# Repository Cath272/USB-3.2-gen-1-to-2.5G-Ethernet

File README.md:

# USB 3.2 gen 1 to 2.5Gb Ethernet
 2.5GbE to USB C using VL162 and RTL8156

 ## VL162

  - 4:2 10Gbps USB Type-C Data Switch

  - Low power consumption with 6mW active at device mode

 ## RTL8156BG 

  - Integrated 10/100/1000M/2.5G transceiver

  - Supports USB 3.0, 2.0, and 1.1

 ## TPS62420

 - 5V to 3.3V DC-DC (600mA)
 - 5V to 0.95V DC-DC (1A)

 ## W25Q16BVSSIG

 - 16Mbit SPI Flash  

 ## LX82405SP
 -2.5GbE Magnetics 
## PCB 
This board uses a 4 layer stackup with a  1.6mm thickness:

- POWER/SIGNAL

- GND
  
- GND
  
- POWER/SIGNAL

High Speed diferential lines need a refrence ground plane so internal planes are ground referance planes for the High speed USB lines

### Schematic:

## PCB Screenshots

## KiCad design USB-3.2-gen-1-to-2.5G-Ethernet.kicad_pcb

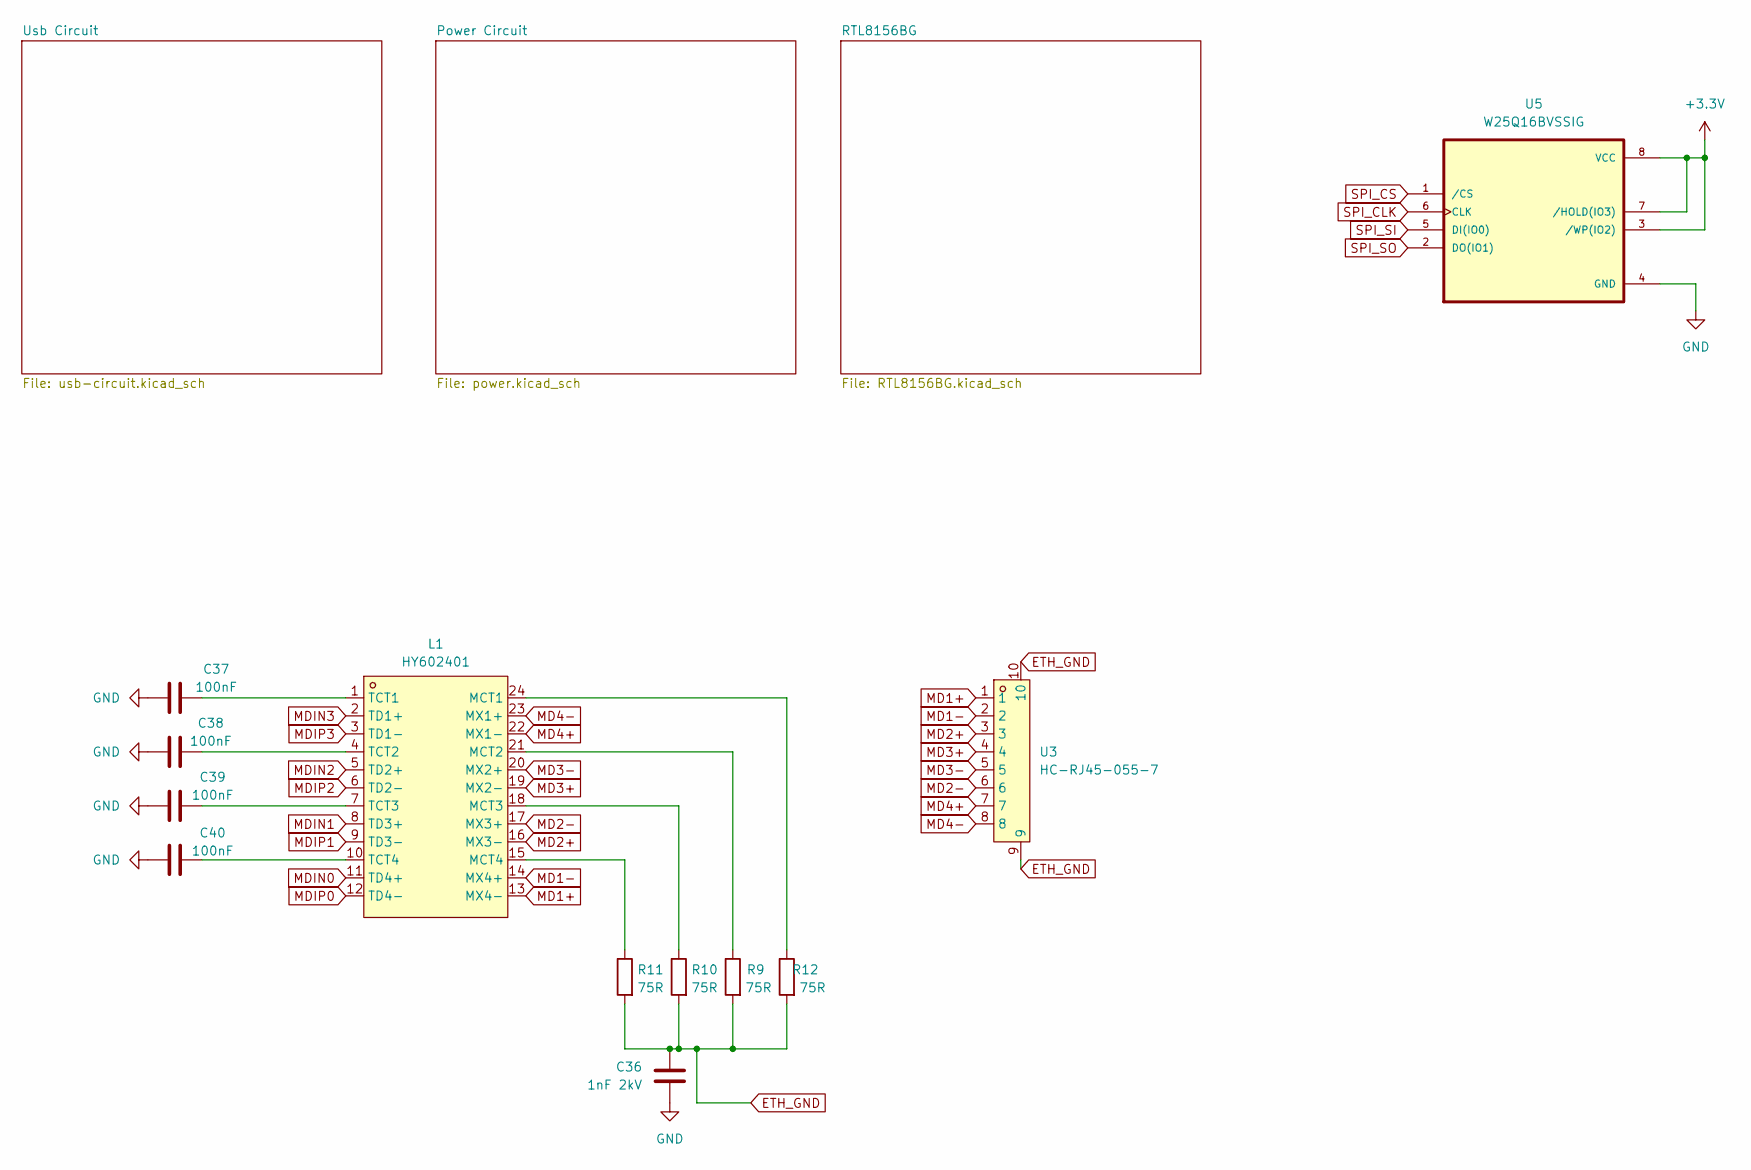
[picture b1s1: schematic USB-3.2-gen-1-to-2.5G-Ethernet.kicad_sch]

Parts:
C36: 1nF 2kV; C_1210_3225Metric
C37, C38, C39, C40: 100nF; C_0402_1005Metric
L1: HY602401; XFMR-SMD_HY602401; LCSC Part C55685
R9, R10, R11, R12: 75R; R_0402_1005Metric
U3: HC-RJ45-055-7; RJ45-SMD_HC-RJ45-055-7_1; LCSC Part C3000213
U5: W25Q16BVSSIG; SOIC-8_L5.3-W5.3-P1.27-LS8.0-BL; PARTREV F

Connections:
+3.3V: U5.3 (/WP(IO2)), U5.7 (/HOLD(IO3)), U5.8 (VCC); also elsewhere on the board
ETH_GND: C36.1, R9.2, R10.2, R11.2, R12.2, U3.9, U3.10
GND: C36.2, C37.2, C38.2, C39.2, C40.2, U5.4 (GND); also elsewhere on the board
LED0: U5.5 (DI(IO0)); also elsewhere on the board
MD1+: L1.13 (MX4-), U3.1
MD1-: L1.14 (MX4+), U3.2
MD2+: L1.16 (MX3-), U3.3
MD2-: L1.17 (MX3+), U3.6
MD3+: L1.19 (MX2-), U3.4
MD3-: L1.20 (MX2+), U3.5
MD4+: L1.22 (MX1-), U3.7
MD4-: L1.23 (MX1+), U3.8
MDIN0: L1.11 (TD4+); also elsewhere on the board
MDIN1: L1.8 (TD3+); also elsewhere on the board
MDIN2: L1.5 (TD2+); also elsewhere on the board
MDIN3: L1.2 (TD1+); also elsewhere on the board
MDIP0: L1.12 (TD4-); also elsewhere on the board
MDIP1: L1.9 (TD3-); also elsewhere on the board
MDIP2: L1.6 (TD2-); also elsewhere on the board
MDIP3: L1.3 (TD1-); also elsewhere on the board
unnamed: L1.24 (MCT1), R12.1
unnamed: L1.21 (MCT2), R9.1
unnamed: L1.18 (MCT3), R10.1
unnamed: L1.15 (MCT4), R11.1
unnamed: C37.1, L1.1 (TCT1)
unnamed: C38.1, L1.4 (TCT2)
unnamed: C39.1, L1.7 (TCT3)
unnamed: C40.1, L1.10 (TCT4)
SPI_CLK: U5.6 (CLK); also elsewhere on the board
SPI_CS: U5.1 (/CS); also elsewhere on the board
SPI_SO: U5.2 (DO(IO1)); also elsewhere on the board

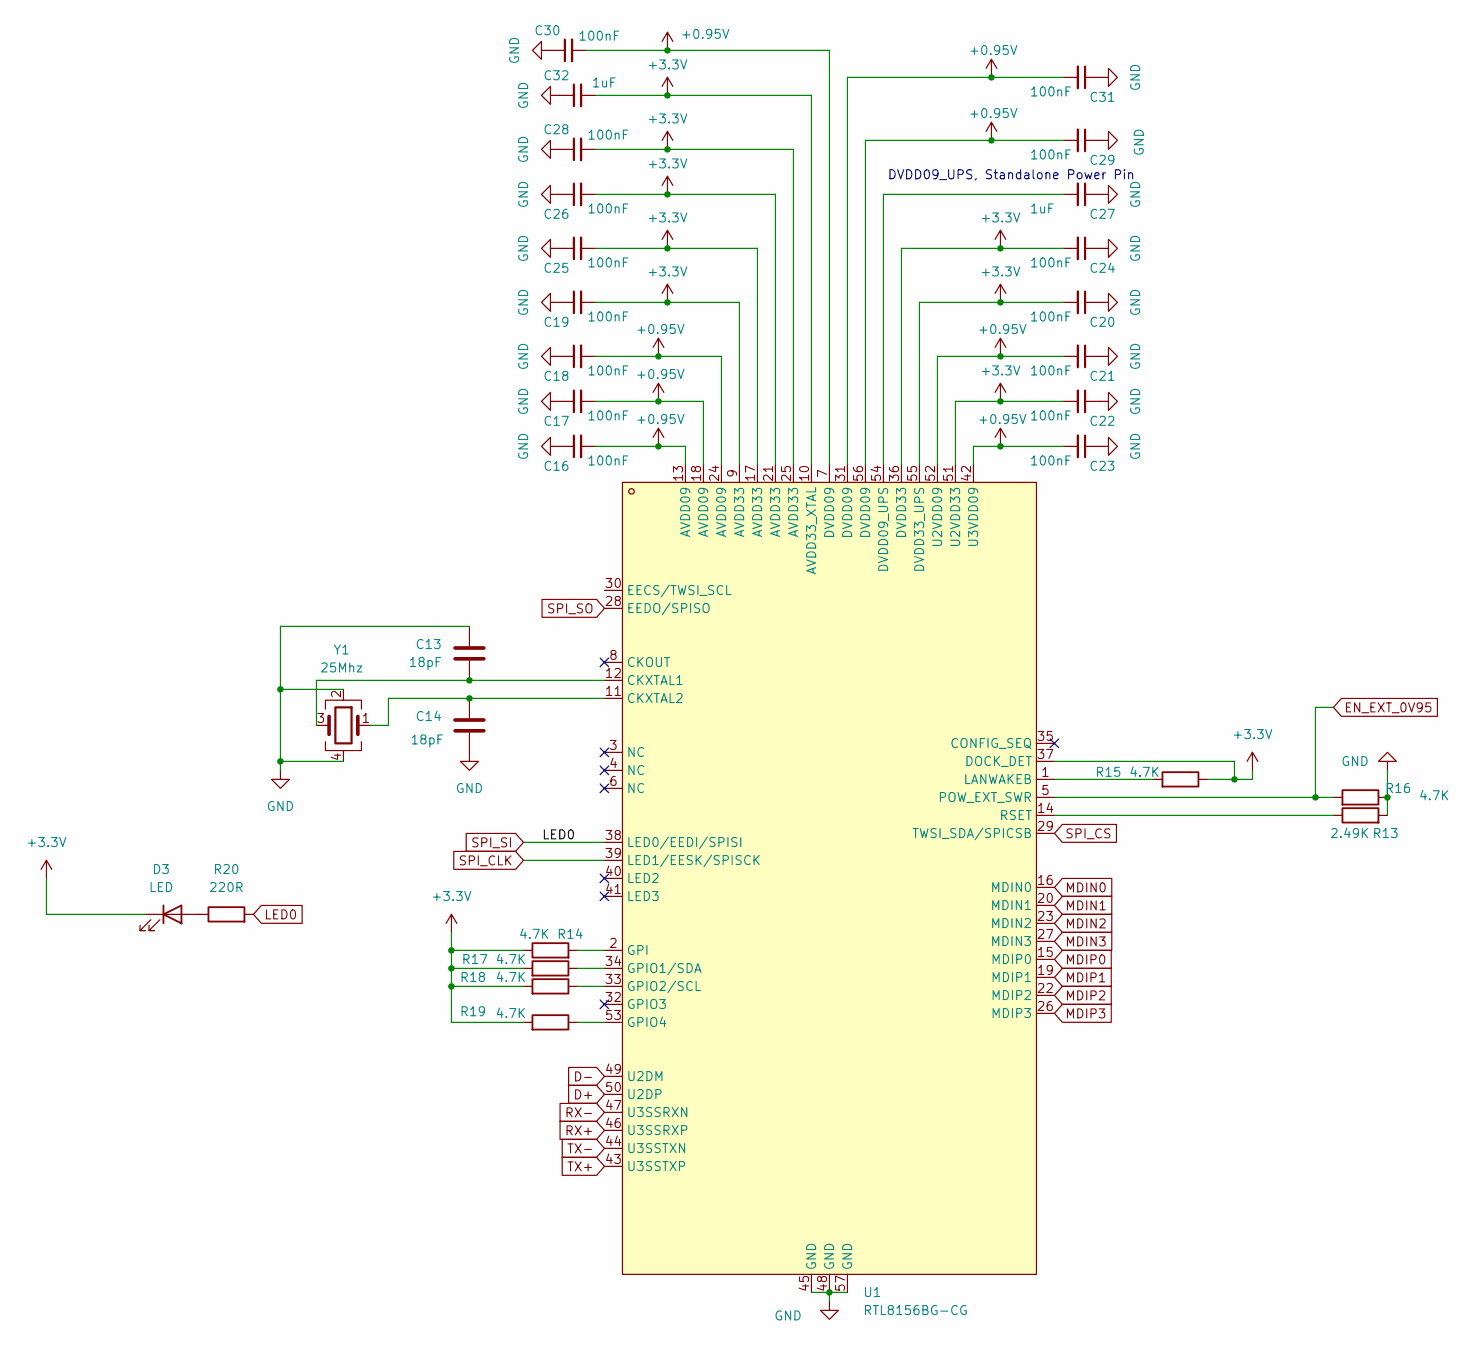
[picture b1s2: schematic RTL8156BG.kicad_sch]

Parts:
C13, C14: 18pF; C_0402_1005Metric
C16, C17, C18, C19, C20, C21, C22, C23, C24, C25, C26, C28, C29, C30, C31: 100nF; C_0402_1005Metric
C27, C32: 1uF; C_0603_1608Metric
D3: LED; LED_0603_1608Metric
R13: 2.49K; R_0402_1005Metric
R14, R15, R16, R17, R18, R19: 4.7K; R_0402_1005Metric
R20: 220R; R_0402_1005Metric
U1: RTL8156BG-CG; QFN-56_L6.0-W6.0-P0.35--TL-EP4.7; LCSC Part C41376388
Y1: 25Mhz; Crystal_SMD_3225-4Pin_3.2x2.5mm

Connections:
+0.95V: C16.2, C17.2, C18.2, C21.2, C23.2, C29.2, C30.2, C31.2, U1.7 (DVDD09), U1.13 (AVDD09), U1.18 (AVDD09), U1.24 (AVDD09), U1.31 (DVDD09), U1.42 (U3VDD09), U1.52 (U2VDD09), U1.56 (DVDD09); also elsewhere on the board
+3.3V: C19.2, C20.2, C22.2, C24.2, C25.2, C26.2, C28.2, C32.2, D3.1 (K), R14.1, R15.1, R17.2, R18.2, R19.2, U1.9 (AVDD33), U1.10 (AVDD33_XTAL), U1.17 (AVDD33), U1.21 (AVDD33), U1.25 (AVDD33), U1.36 (DVDD33), U1.37 (DOCK_DET), U1.51 (U2VDD33), U1.55 (DVDD33_UPS); also elsewhere on the board
D+: U1.50 (U2DP); also elsewhere on the board
D-: U1.49 (U2DM); also elsewhere on the board
EN_EXT_0V95: R16.2, U1.5 (POW_EXT_SWR); also elsewhere on the board
GND: C13.1, C14.2, C16.1, C17.1, C18.1, C19.1, C20.1, C21.1, C22.1, C23.1, C24.1, C25.1, C26.1, C27.1, C28.1, C29.1, C30.1, C31.1, C32.1, R13.2, R16.1, U1.45 (GND), U1.48 (GND), U1.57 (GND), Y1.2, Y1.4; also elsewhere on the board
LED0: R20.2, U1.38 (LED0/EEDI/SPISI); also elsewhere on the board
MDIN0: U1.16 (MDIN0); also elsewhere on the board
MDIN1: U1.20 (MDIN1); also elsewhere on the board
MDIN2: U1.23 (MDIN2); also elsewhere on the board
MDIN3: U1.27 (MDIN3); also elsewhere on the board
MDIP0: U1.15 (MDIP0); also elsewhere on the board
MDIP1: U1.19 (MDIP1); also elsewhere on the board
MDIP2: U1.22 (MDIP2); also elsewhere on the board
MDIP3: U1.26 (MDIP3); also elsewhere on the board
unnamed: D3.2 (A), R20.1
unnamed: C13.2, U1.12 (CKXTAL1), Y1.3
unnamed: C14.1, U1.11 (CKXTAL2), Y1.1
unnamed: C27.2, U1.54 (DVDD09_UPS)
unnamed: R14.2, U1.2 (GPI)
unnamed: R17.1, U1.34 (GPIO1/SDA)
unnamed: R18.1, U1.33 (GPIO2/SCL)
unnamed: R19.1, U1.53 (GPIO4)
unnamed: R15.2, U1.1 (LANWAKEB)
unnamed: R13.1, U1.14 (RSET)
RX+: U1.46 (U3SSRXP); also elsewhere on the board
RX-: U1.47 (U3SSRXN); also elsewhere on the board
SPI_CLK: U1.39 (LED1/EESK/SPISCK); also elsewhere on the board
SPI_CS: U1.29 (TWSI_SDA/SPICSB); also elsewhere on the board
SPI_SO: U1.28 (EEDO/SPISO); also elsewhere on the board
TX+: U1.43 (U3SSTXP); also elsewhere on the board
TX-: U1.44 (U3SSTXN); also elsewhere on the board

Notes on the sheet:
DVDD09_UPS, Standalone Power Pin

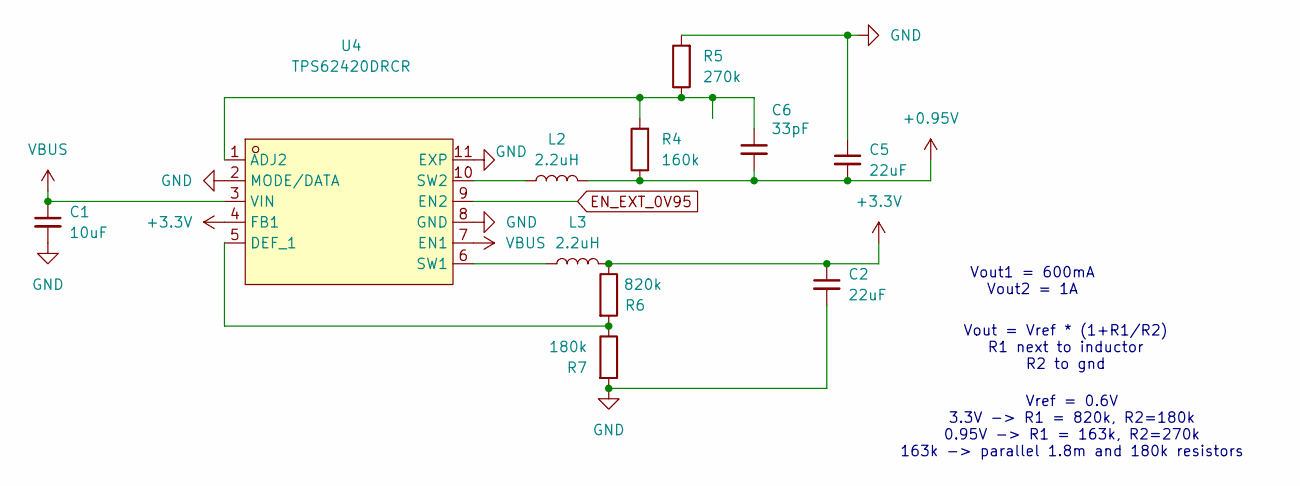
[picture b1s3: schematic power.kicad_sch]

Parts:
C1: 10uF; C_0805_2012Metric
C2, C5: 22uF; C_0805_2012Metric
C6: 33pF; C_0402_1005Metric
L2, L3: 2.2uH; IND-SMD_L3.5-W3.0
R4: 160k; R_0402_1005Metric
R5: 270k; R_0402_1005Metric
R6: 820k; R_0402_1005Metric
R7: 180k; R_0402_1005Metric
U4: TPS62420DRCR; VSON-10_L3.0-W3.0-P0.50-TL-EP; LCSC Part C74233

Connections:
+0.95V: C5.2, C6.2, L2.2, R4.1; also elsewhere on the board
+3.3V: C2.1, L3.2, R6.1, U4.4 (FB1); also elsewhere on the board
EN_EXT_0V95: U4.9 (EN2); also elsewhere on the board
GND: C1.2, C2.2, C5.1, R5.2, R7.2, U4.2 (MODE/DATA), U4.8 (GND), U4.11 (EXP); also elsewhere on the board
unnamed: C6.1, R4.2, R5.1, U4.1 (ADJ2)
unnamed: R6.2, R7.1, U4.5 (DEF_1)
unnamed: L3.1, U4.6 (SW1)
unnamed: L2.1, U4.10 (SW2)
VBUS: C1.1, U4.3 (VIN), U4.7 (EN1); also elsewhere on the board

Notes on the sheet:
Vref = 0.6V 3.3V -> R1 = 820k, R2=180k 0.95V -> R1 = 163k, R2=270k 163k -> parallel 1.8m and 180k resistors
Vout = Vref * (1+R1/R2) R1 next to inductor R2 to gnd
Vout1 = 600mA Vout2 = 1A

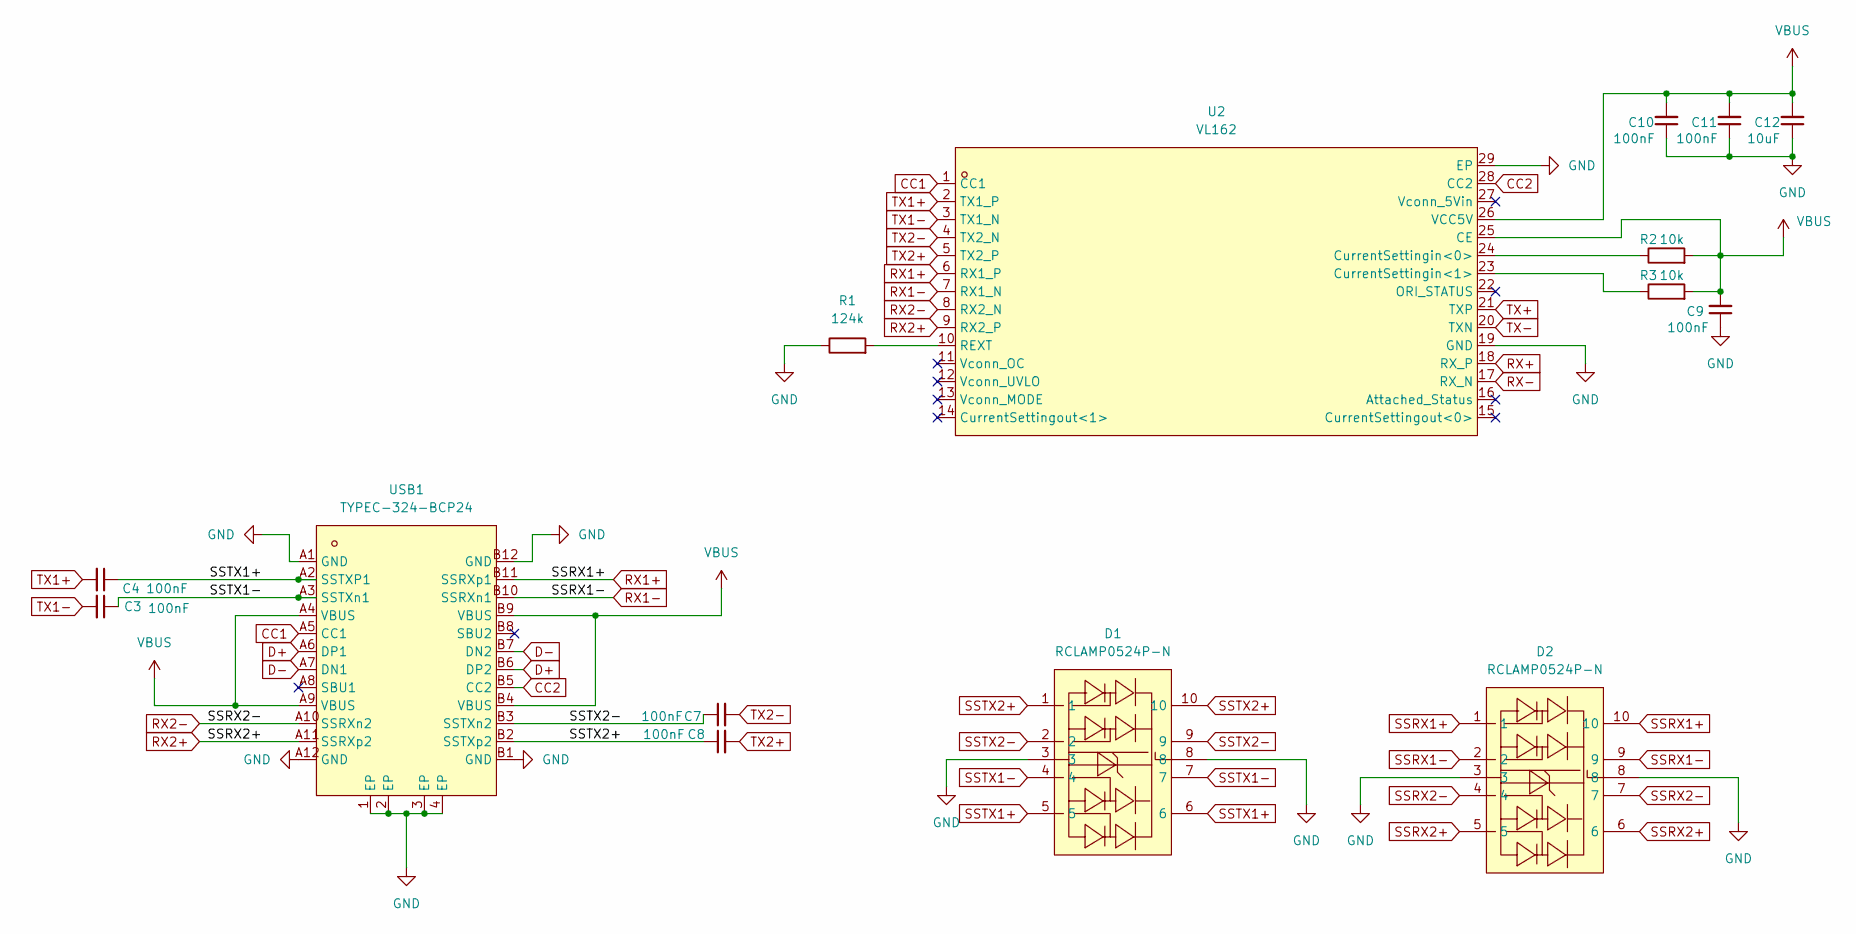
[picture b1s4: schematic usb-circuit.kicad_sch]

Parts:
C3, C4, C7, C8, C9, C10, C11: 100nF; C_0402_1005Metric
C12: 10uF; C_0805_2012Metric
D1, D2: RCLAMP0524P-N; DFN-10L_L2.5-W1.0-P0.50-BL; LCSC Part C316044
R1: 124k; R_0402_1005Metric
R2, R3: 10k; R_0402_1005Metric
U2: VL162; MQFN-28_L4.5-W3.5-P0.40-BL-EP; LCSC Part C19270896
USB1: TYPEC-324-BCP24; USB-C-SMD_TYPEC-324-BCP24; LCSC Part C2835314

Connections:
CC1: U2.1 (CC1), USB1.A5 (CC1)
CC2: U2.28 (CC2), USB1.B5 (CC2)
D+: USB1.A6 (DP1), USB1.B6 (DP2); also elsewhere on the board
D-: USB1.A7 (DN1), USB1.B7 (DN2); also elsewhere on the board
GND: C9.1, C10.1, C11.1, C12.1, D1.3, D1.8, D2.3, D2.8, R1.1, U2.19 (GND), U2.29 (EP), USB1.1 (EP), USB1.2 (EP), USB1.3 (EP), USB1.4 (EP), USB1.A1 (GND), USB1.A12 (GND), USB1.B1 (GND), USB1.B12 (GND); also elsewhere on the board
unnamed: R2.1, U2.24 (CurrentSettingin<0>)
unnamed: R3.1, U2.23 (CurrentSettingin<1>)
unnamed: R1.2, U2.10 (REXT)
RX1+: D2.1, D2.10, U2.6 (RX1_P), USB1.B11 (SSRXp1)
RX1-: D2.2, D2.9, U2.7 (RX1_N), USB1.B10 (SSRXn1)
RX2+: D2.5, D2.6, U2.9 (RX2_P), USB1.A11 (SSRXp2)
RX2-: D2.4, D2.7, U2.8 (RX2_N), USB1.A10 (SSRXn2)
RX+: U2.18 (RX_P); also elsewhere on the board
RX-: U2.17 (RX_N); also elsewhere on the board
SSTX1+: C4.1, D1.5, D1.6, USB1.A2 (SSTXP1)
SSTX1-: C3.1, D1.4, D1.7, USB1.A3 (SSTXn1)
SSTX2+: C8.1, D1.1, D1.10, USB1.B2 (SSTXp2)
SSTX2-: C7.1, D1.2, D1.9, USB1.B3 (SSTXn2)
TX1+: C4.2, U2.2 (TX1_P)
TX1-: C3.2, U2.3 (TX1_N)
TX2+: C8.2, U2.5 (TX2_P)
TX2-: C7.2, U2.4 (TX2_N)
TX+: U2.21 (TXP); also elsewhere on the board
TX-: U2.20 (TXN); also elsewhere on the board
VBUS: C9.2, C10.2, C11.2, C12.2, R2.2, R3.2, U2.25 (CE), U2.26 (VCC5V), USB1.A4 (VBUS), USB1.A9 (VBUS), USB1.B4 (VBUS), USB1.B9 (VBUS); also elsewhere on the board

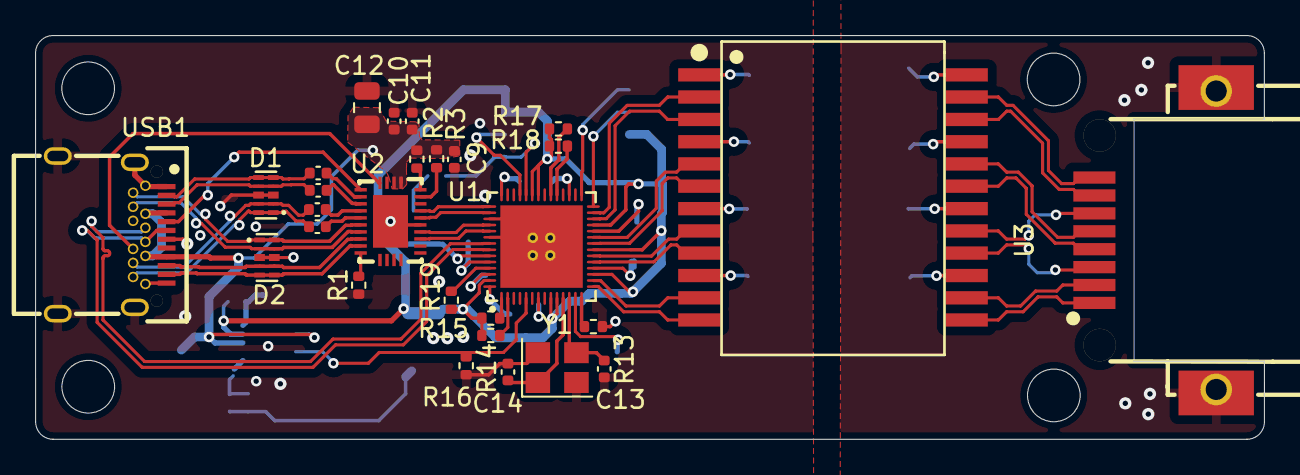
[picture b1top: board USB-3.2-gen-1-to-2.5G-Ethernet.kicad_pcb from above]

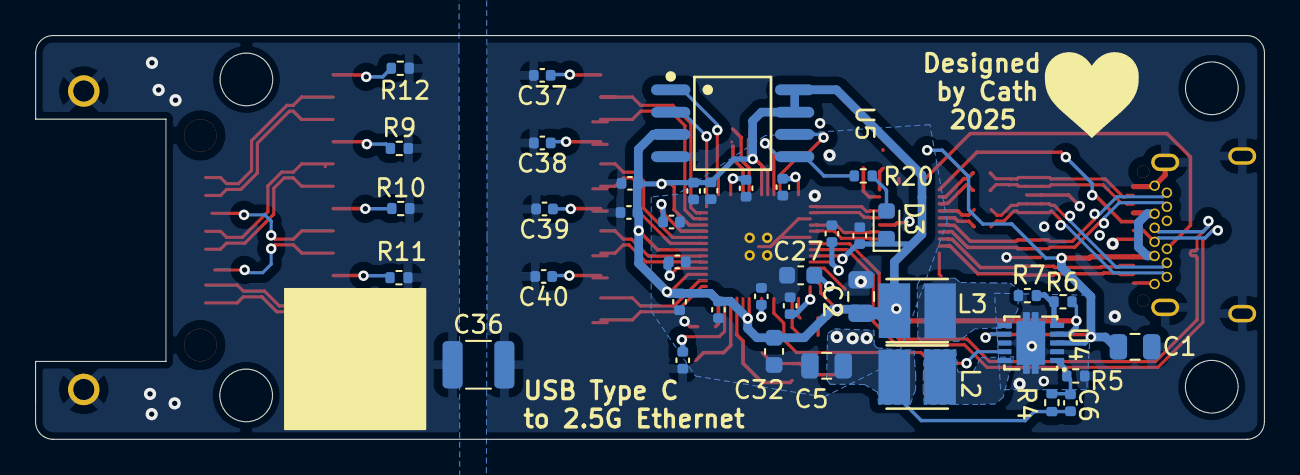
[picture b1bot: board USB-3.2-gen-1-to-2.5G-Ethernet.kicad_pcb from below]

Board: 4 copper layers, 70.0 x 23.0 mm, 68 parts (40 on the bottom side), 71 nets.

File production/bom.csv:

Designator,Footprint,Quantity,Value,LCSC Part #
"C1, C12",0805,2,10uF,
"C10, C11, C16, C17, C18, C19, C20, C21, C22, C23, C24, C25, C26, C28, C29, C3, C30, C31, C37, C38, C39, C4, C40, C7, C8, C9",0402,26,100nF,
"C13, C14",0402,2,18pF,
"C2, C5",0805,2,22uF,
"C27, C32",0603,2,1uF,
C36,1210,1,1nF 2kV,
C6,0402,1,33pF,
"D1, D2",DFN-10L_L2.5-W1.0-P0.50-BL,2,RCLAMP0524P-N,C316044
D3,0603,1,LED,
L1,XFMR-SMD_HY602401,1,HY602401,C55685
"L2, L3",IND-SMD_L3.5-W3.0,2,2.2uH,
R1,0402,1,124k,
"R10, R11, R12, R9",0402,4,75R,
R13,0402,1,2.49K,
"R14, R15, R16, R17, R18, R19",0402,6,4.7K,
"R2, R3",0402,2,10k,
R20,0402,1,220R,
"R4, R7",0402,2,180k,
R5,0402,1,280k,
R6,0402,1,910k,
R8,0402,1,1.8M,
U1,QFN-56_L6.0-W6.0-P0.35--TL-EP4.7,1,RTL8156BG-CG,C41376388
U2,MQFN-28_L4.5-W3.5-P0.40-BL-EP,1,VL162,C19270896
U3,RJ45-SMD_HC-RJ45-055-7_1,1,HC-RJ45-055-7,C3000213
U4,VSON-10_L3.0-W3.0-P0.50-TL-EP,1,TPS62420DRCR,C74233
U5,SOIC-8_L5.3-W5.3-P1.27-LS8.0-BL,1,W25Q16BVSSIG,
USB1,USB-C-SMD_TYPEC-324-BCP24,1,TYPEC-324-BCP24,C2835314
Y1,Crystal_SMD_3225-4Pin_3.2x2.5mm,1,25Mhz,

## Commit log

2025-07-15 Revert "Initial commit"
    This reverts commit 5fe75af51c81b825b2ffe87a5b72ef0963907a4b.
2025-07-15 Updated pics
